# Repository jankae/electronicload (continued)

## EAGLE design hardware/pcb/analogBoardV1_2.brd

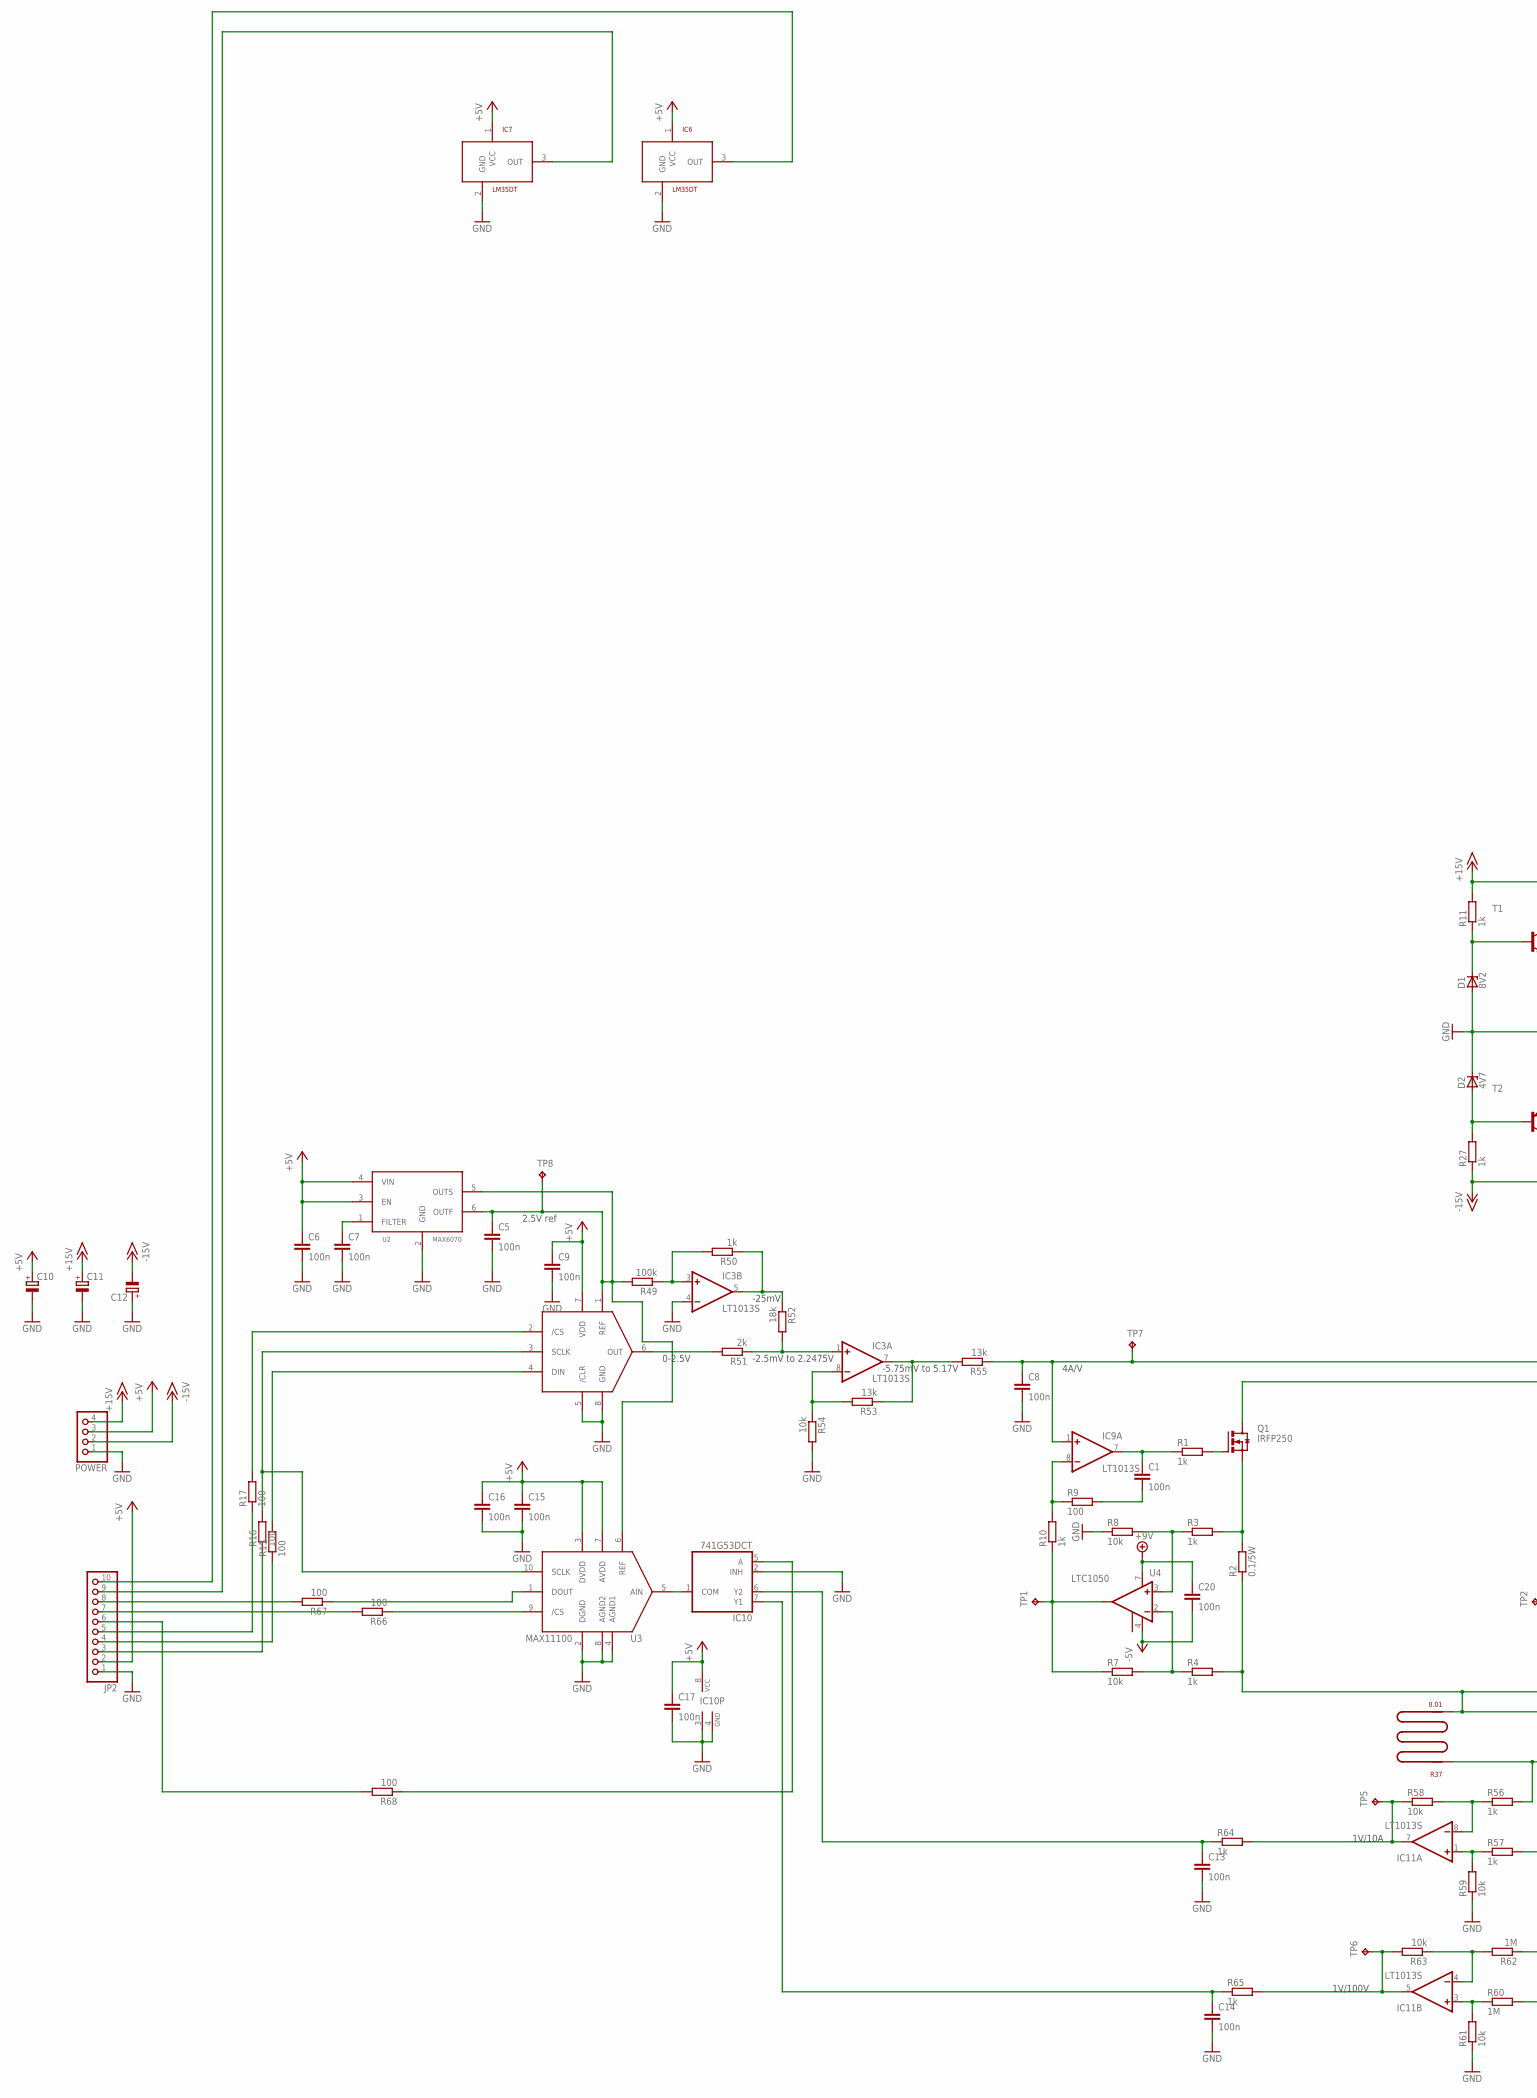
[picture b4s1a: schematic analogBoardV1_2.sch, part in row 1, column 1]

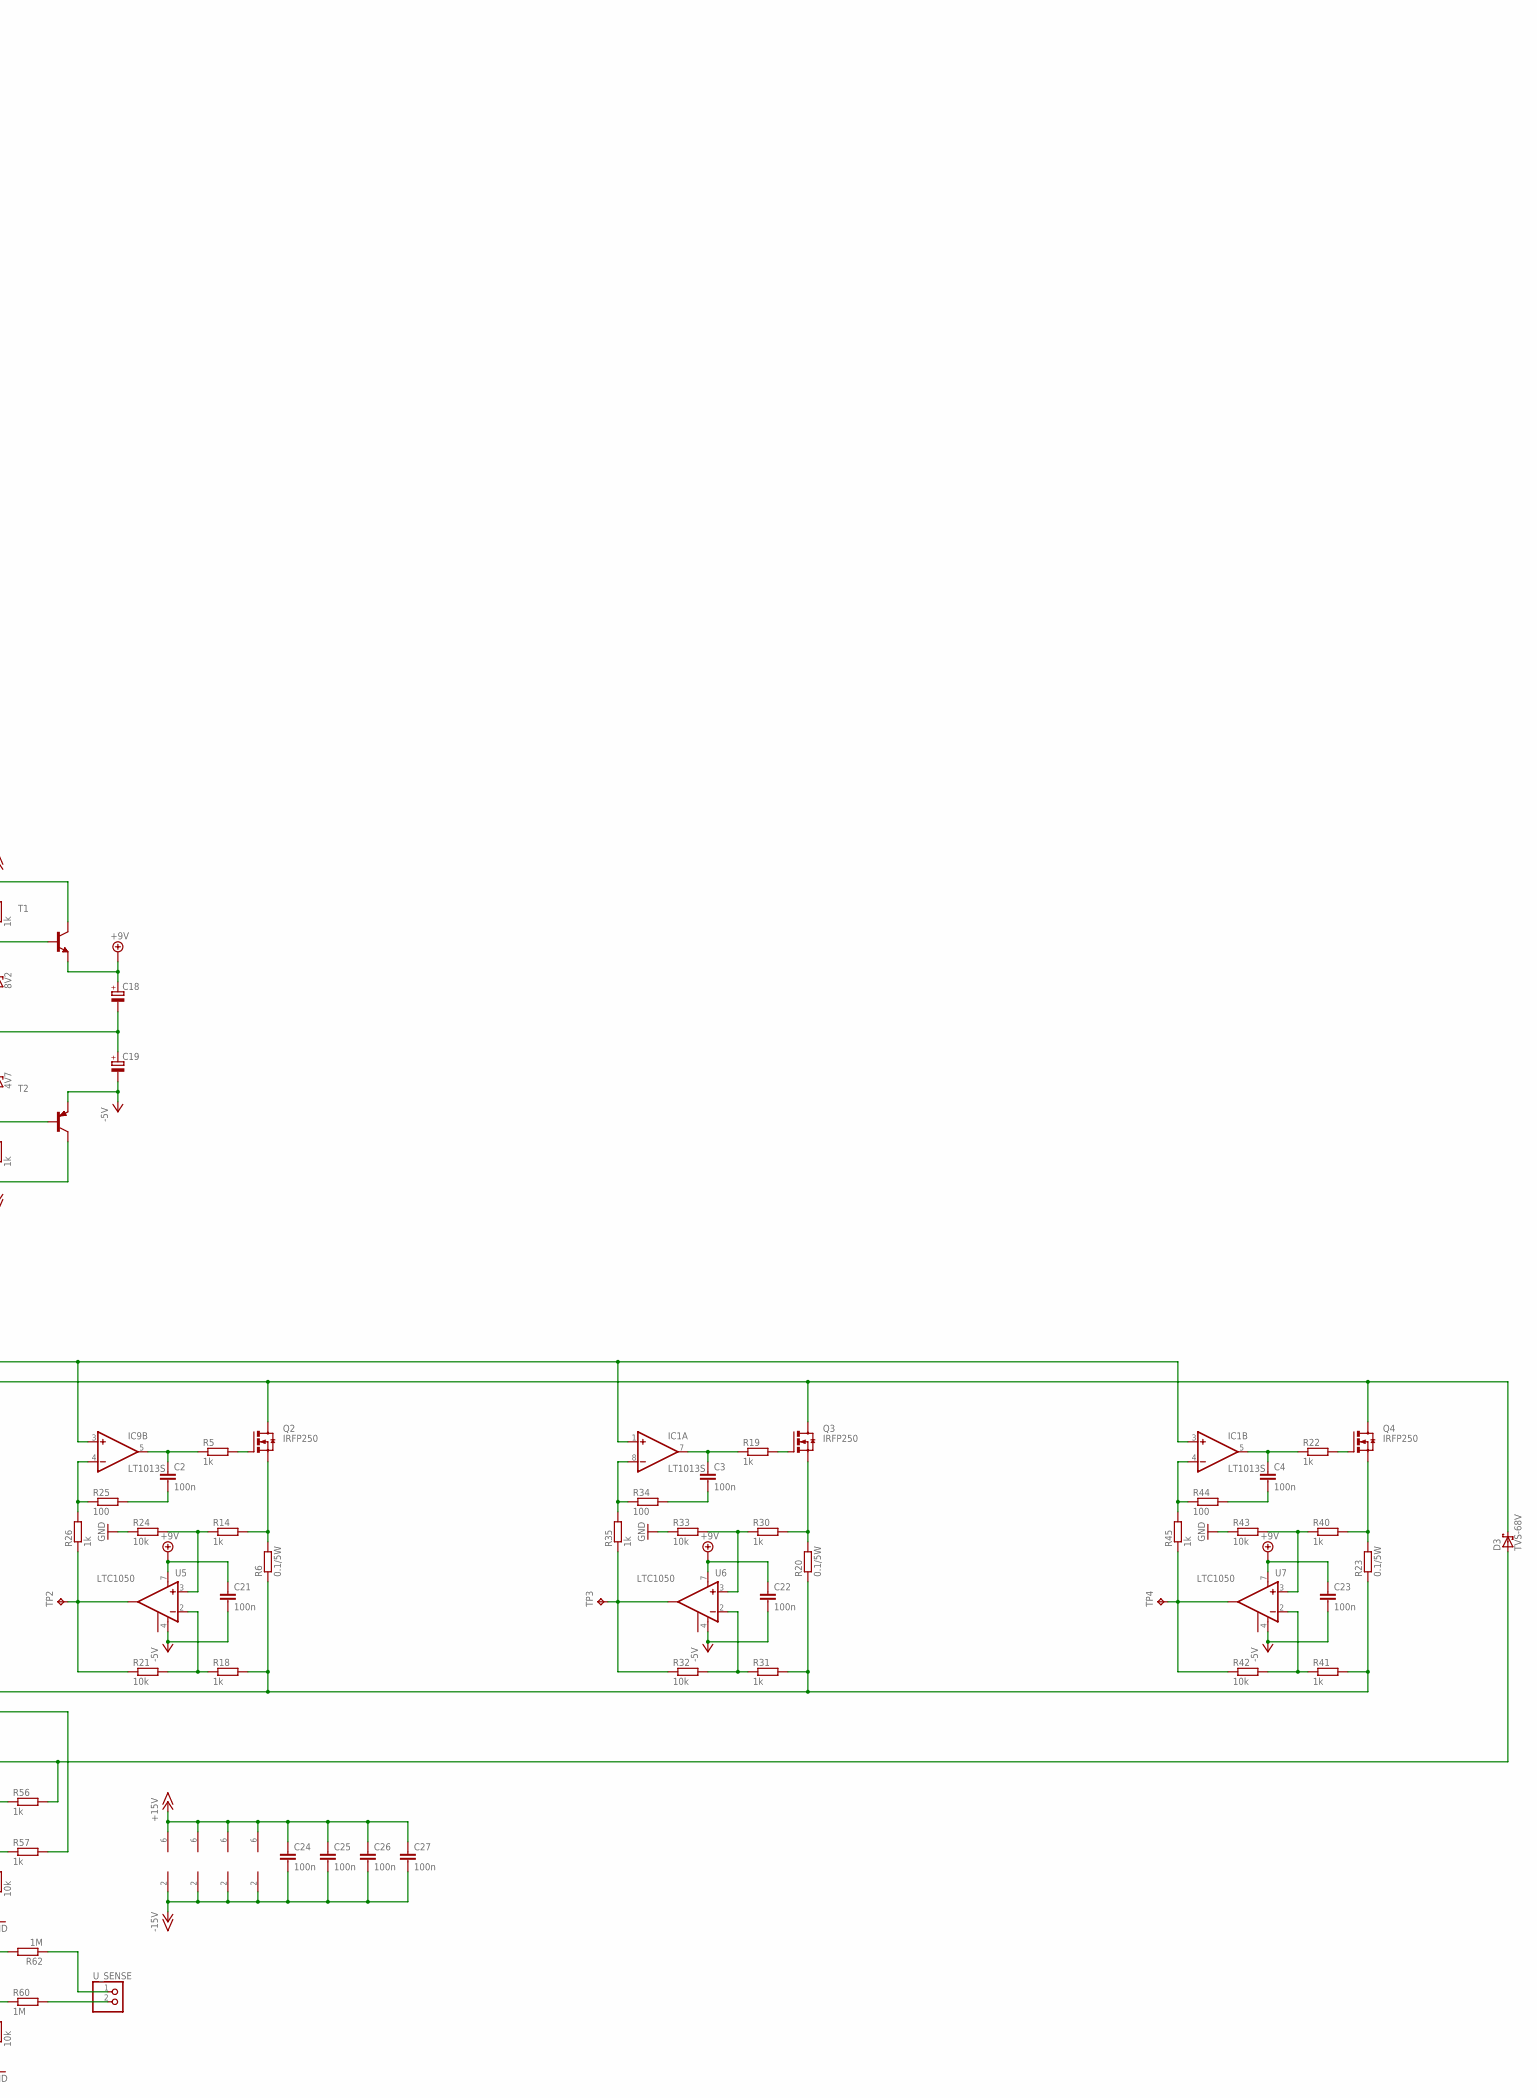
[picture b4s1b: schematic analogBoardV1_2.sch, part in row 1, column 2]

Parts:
C1, C2, C3, C4, C5, C6, C7, C8, C9, C13, C14, C15, C16, C17, C20, C21, C22, C23, C24, C25, C26, C27: 100n; C0603K
C10, C11, C12, C18, C19: CPOL-EUE2.5-6; E2,5-6
D1: 8V2; SOT23
D2: 4V7; SOT23
D3: TVS-68V; CB429-15
IC1, IC3, IC9, IC11: LT1013S; SO08
IC6, IC7: LM35DT; TO220V
IC10: 741G53DCT; DCT_R-PDSO-G8
JP2: PINHD-1X10; 1X10
POWER: PINHD-1X4; 1X04
Q1, Q2, Q3, Q4: IRFP250; TO-247AD-V
R1, R3, R4, R5, R10, R11, R14, R18, R19, R22, R26, R27, R30, R31, R35, R40, R41, R45, R50, R56, R57, R64, R65: 1k; R0603
R2, R6, R20, R23: 0.1/5W; 5WAXIAL
R7, R8, R21, R24, R32, R33, R42, R43, R54, R58, R59, R61, R63: 10k; R0603
R9, R15, R16, R17, R25, R34, R44, R66, R67, R68: 100; R0603
R37: 0.01; COPPERSHUNT
R49: 100k; R0603
R51: 2k; R0603
R52: 18k; R0603
R53, R55: 13k; R0603
R60, R62: 1M; R0603
T1: BC817-16-NPN-SOT23-BEC; SOT23-BEC
T2: BC807-16-PNP-SOT23-BEC; SOT23-BEC
TP1, TP2, TP3, TP4, TP5, TP6, TP7, TP8: TPB1,27; B1,27
U1: MAX5216; UMAX8
U2: MAX6070; SOT23-6L
U3: MAX11100; UMAX10
U4, U5, U6, U7: LTC1050; SOIC8
U_SENSE: PINHD-1X2; 1X02

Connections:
1M: R62.1, U_SENSE.1
+5V: C6.1, C9.1, C10.+, C15.1, C16.1, C17.1, IC6.1 (VCC), IC7.1 (VCC), IC10.8 (VCC), JP2.2, POWER.3, U1.7 (VDD), U2.3 (EN), U2.4 (VIN), U3.3 (DVDD), U3.7 (AVDD)
+9V: C18.+, C20.1, C21.1, C22.1, C23.1, T1.E, U4.7 (V+), U5.7 (V+), U6.7 (V+), U7.7 (V+)
+15V: C11.+, C24.1, C25.1, C26.1, C27.1, IC1.6 (V+), IC3.6 (V+), IC9.6 (V+), IC11.6 (V+), POWER.4, R11.2, T1.C
-5V: C19.-, C20.2, C21.2, C22.2, C23.2, T2.E, U4.4 (V-), U5.4 (V-), U6.4 (V-), U7.4 (V-)
-15V: C12.-, C24.2, C25.2, C26.2, C27.2, IC1.2 (V-), IC3.2 (V-), IC9.2 (V-), IC11.2 (V-), POWER.2, R27.1, T2.C
GND: C5.2, C6.2, C7.2, C8.2, C9.2, C10.-, C11.-, C12.+, C13.2, C14.2, C15.2, C16.2, C17.2, C18.-, C19.+, D1.1 (A), D2.3 (C), IC3.4 (-IN), IC6.2 (GND), IC7.2 (GND), IC10.2 (INH), IC10.3 (GND), IC10.4 (GND), JP2.1, POWER.1, R8.1, R24.1, R33.1, R43.1, R54.2, R59.1, R61.1, U1.5 (/CLR), U1.8 (GND), U2.2 (GND), U3.2 (DGND), U3.4 (AGND1), U3.8 (AGND2)
unnamed: R2.1, R4.2, R6.1, R18.2, R20.1, R23.1, R31.2, R37.P$2, R41.2, R57.2
unnamed: Q1.G, R1.2
unnamed: Q1.S, R2.2, R3.2
unnamed: R4.1, R7.2, U4.2 (-IN)
unnamed: R3.1, R8.2, U4.3 (+IN)
unnamed: Q2.G, R5.2
unnamed: Q2.S, R6.2, R14.2
unnamed: C1.1, IC9.7 (OUT), R1.1
unnamed: C1.2, R9.2
unnamed: R7.1, R10.1, TP1.TP, U4.6 (OUT)
unnamed: IC9.8 (-IN), R9.1, R10.2
unnamed: D1.3 (C), R11.1, T1.B
unnamed: D2.1 (A), R27.2, T2.B
unnamed: Q3.G, R19.2
unnamed: R15.2, U1.4 (DIN)
unnamed: Q3.S, R20.2, R30.2
unnamed: R16.2, U1.3 (SCLK), U3.10 (SCLK)
unnamed: R17.2, U1.2 (/CS)
unnamed: C8.1, IC1.1 (+IN), IC1.3 (+IN), IC9.1 (+IN), IC9.3 (+IN), R55.1, TP7.TP
unnamed: C7.1, U2.1 (FILTER)
unnamed: Q4.G, R22.2
unnamed: Q4.S, R23.2, R40.2
unnamed: C5.1, R49.2, TP8.TP, U1.1 (REF), U2.5 (OUTS), U2.6 (OUTF), U3.6 (REF)
unnamed: R51.2, U1.6 (OUT)
unnamed: R18.1, R21.2, U5.2 (-IN)
unnamed: R14.1, R24.2, U5.3 (+IN)
unnamed: C2.1, IC9.5 (OUT), R5.1
unnamed: C2.2, R25.2
unnamed: R21.1, R26.1, TP2.TP, U5.6 (OUT)
unnamed: IC9.4 (-IN), R25.1, R26.2
unnamed: IC3.3 (+IN), R49.1, R50.2
unnamed: IC3.5 (OUT), R50.1, R52.1
unnamed: IC3.1 (+IN), R51.1, R52.2
unnamed: IC3.8 (-IN), R53.2, R54.1
unnamed: R31.1, R32.2, U6.2 (-IN)
unnamed: R30.1, R33.2, U6.3 (+IN)
unnamed: C3.1, IC1.7 (OUT), R19.1
unnamed: JP2.5, R17.1
unnamed: JP2.3, R16.1
unnamed: JP2.4, R15.1
unnamed: C3.2, R34.2
unnamed: IC6.3 (OUT), JP2.10
unnamed: IC7.3 (OUT), JP2.9
unnamed: R32.1, R35.1, TP3.TP, U6.6 (OUT)
unnamed: IC1.8 (-IN), R34.1, R35.2
unnamed: IC3.7 (OUT), R53.1, R55.2
unnamed: IC10.1 (COM), U3.5 (AIN)
unnamed: R41.1, R42.2, U7.2 (-IN)
unnamed: R40.1, R43.2, U7.3 (+IN)
unnamed: C4.1, IC1.5 (OUT), R22.1
unnamed: C4.2, R44.2
unnamed: R42.1, R45.1, TP4.TP, U7.6 (OUT)
unnamed: IC1.4 (-IN), R44.1, R45.2
unnamed: D3.A, R37.P$1, R56.2
unnamed: IC11.5 (OUT), R63.2, R65.2, TP6.TP
unnamed: IC11.8 (-IN), R56.1, R58.2
unnamed: IC11.1 (+IN), R57.1, R59.2
unnamed: C13.1, IC10.6 (Y2), R64.1
unnamed: IC11.7 (OUT), R58.1, R64.2, TP5.TP
unnamed: R60.2, U_SENSE.2
unnamed: IC11.3 (+IN), R60.1, R61.2
unnamed: IC11.4 (-IN), R62.2, R63.1
unnamed: C14.1, IC10.7 (Y1), R65.1
unnamed: IC10.5 (A), R68.1
unnamed: JP2.7, R66.2
unnamed: R67.1, U3.1 (DOUT)
unnamed: R66.1, U3.9 (/CS)
unnamed: JP2.8, R67.2
unnamed: JP2.6, R68.2
POS_INPUT1: D3.C, Q1.D, Q2.D, Q3.D, Q4.D

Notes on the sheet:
4A/V
0-2.5V
2.5V ref
-25mV
-2.5mV to 2.2475V
-5.75mV to 5.17V
1V/10A
1V/100V

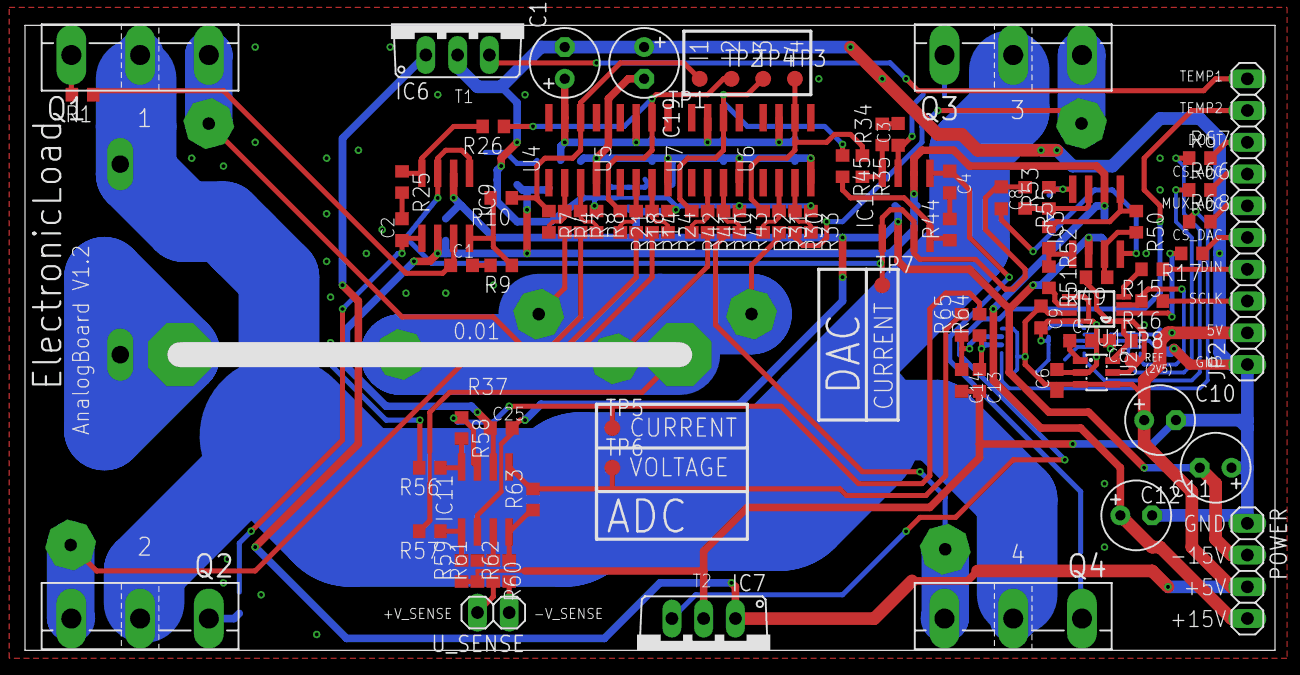
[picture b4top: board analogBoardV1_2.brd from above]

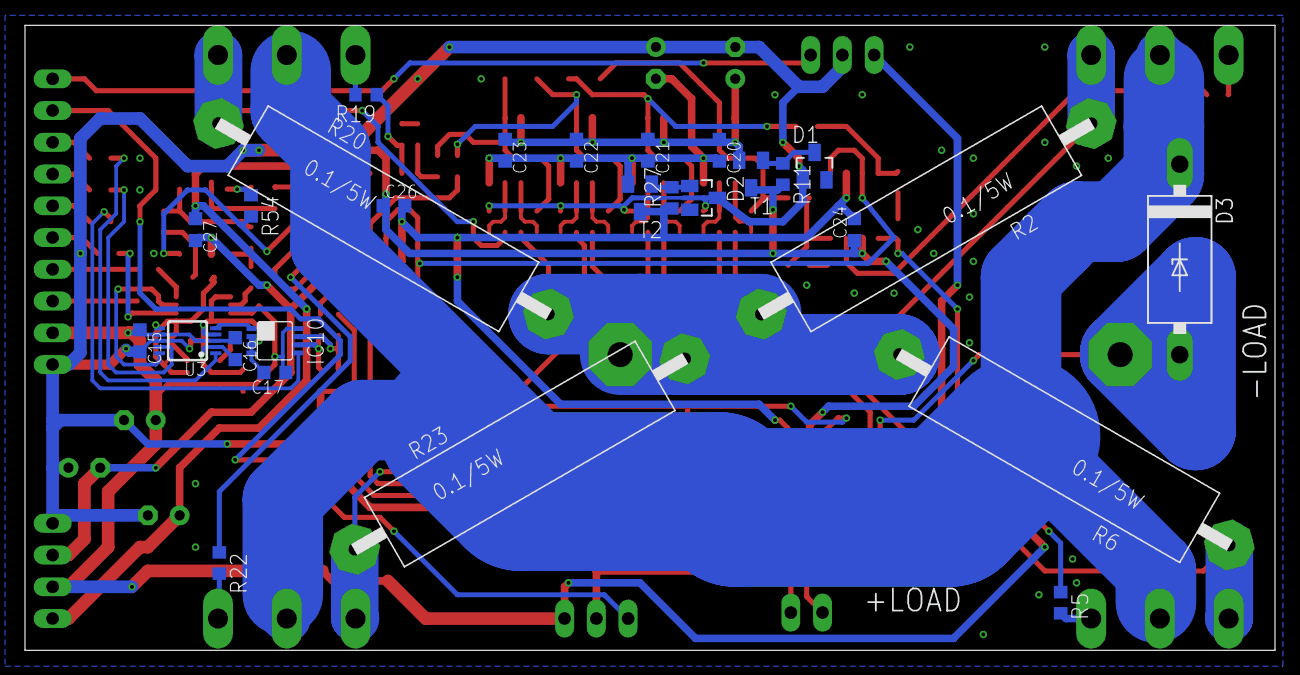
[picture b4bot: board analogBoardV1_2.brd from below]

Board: 2 copper layers, 100.0 x 50.0 mm, 119 parts (27 on the bottom side), 77 nets.

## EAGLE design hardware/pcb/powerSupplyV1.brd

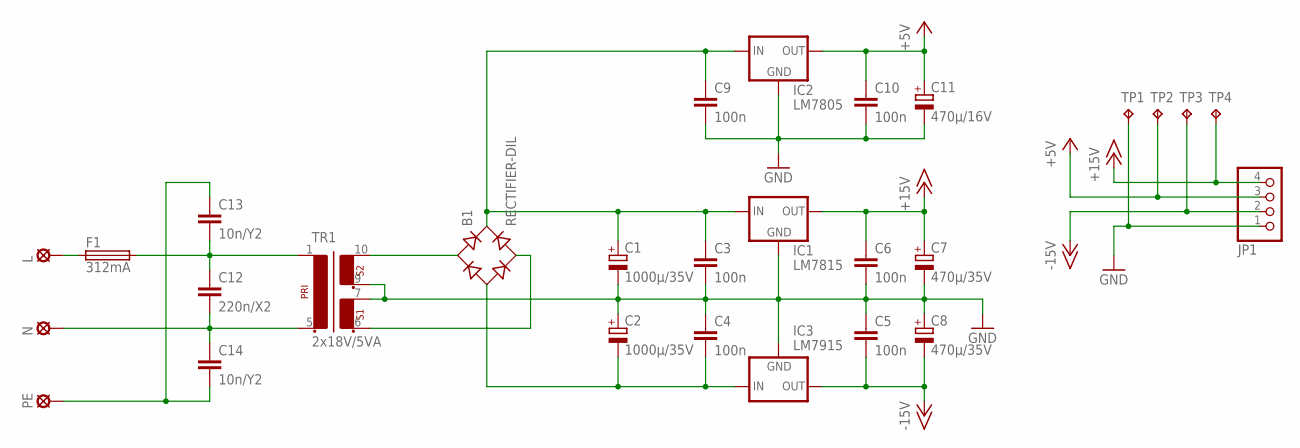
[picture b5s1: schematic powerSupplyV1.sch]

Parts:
B1: RECTIFIER-DIL; B-DIL
C1, C2: 1000µ/35V; E5-13
C3, C4, C5, C6, C9, C10: 100n; C0603K
C7, C8: 470µ/35V; E5-10,5
C11: 470µ/16V; E5-10,5
C12: 220n/X2; C225-062X268
C13, C14: 10n/Y2; C150-054X183
F1: 312mA; SH22,5
IC1: LM7815; 78XXS
IC2: LM7805; 78XXS
IC3: LM7915; 79XXS
JP1: PINHD-1X4; 1X04
L: L; SE14
N: SE14
PE: SE14
TP1, TP2, TP3, TP4: TPB2,54; B2,54
TR1: 2x18V/5VA; EI42-2

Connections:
+5V: C10.1, C11.+, IC2.OUT, JP1.3, TP2.TP
+15V: C6.1, C7.+, IC1.OUT, JP1.4, TP4.TP
-15V: C5.2, C8.-, IC3.OUT, JP1.2, TP3.TP
GND: C1.-, C2.+, C3.2, C4.1, C5.1, C6.2, C7.-, C8.+, C9.2, C10.2, C11.-, IC1.GND, IC2.GND, IC3.GND, JP1.1, TP1.TP, TR1.7 (4), TR1.9 (5)
unnamed: B1.AC1, TR1.10 (6)
unnamed: B1.AC2, TR1.6 (3)
unnamed: C12.1, C13.2, F1.2, TR1.1
unnamed: B1.-, C2.-, C4.2, IC3.IN
unnamed: B1.+, C1.+, C3.1, C9.1, IC1.IN, IC2.IN
unnamed: C12.2, C14.1, N.MP, TR1.5 (2)
unnamed: C13.1, C14.2, PE.MP
unnamed: F1.1, L.MP

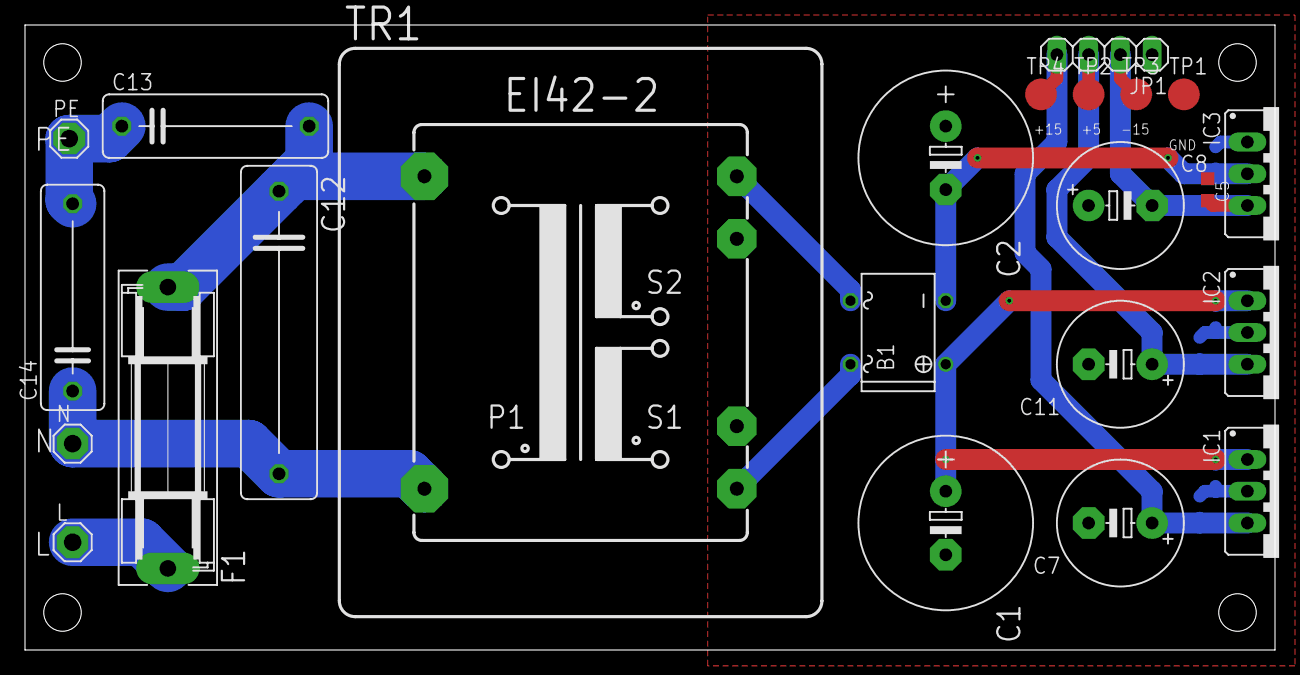
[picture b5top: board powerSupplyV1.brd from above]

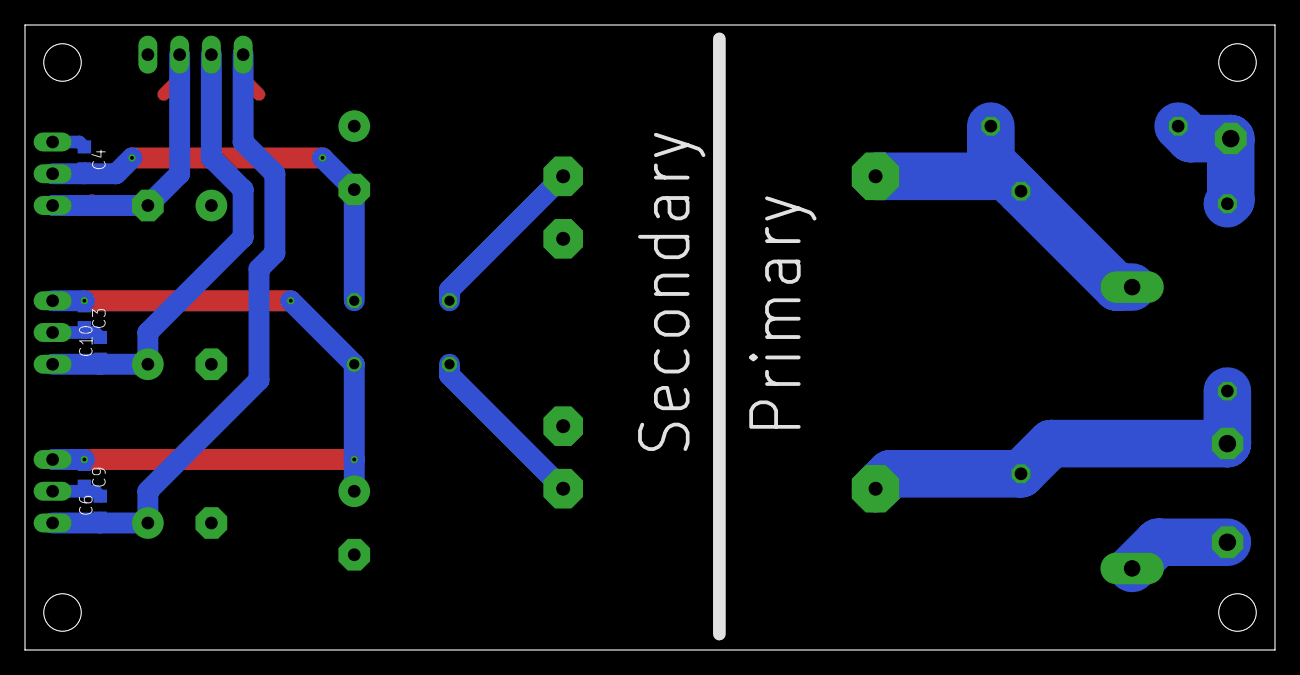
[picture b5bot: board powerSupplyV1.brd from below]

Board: 2 copper layers, 100.0 x 50.0 mm, 28 parts (5 on the bottom side), 12 nets.

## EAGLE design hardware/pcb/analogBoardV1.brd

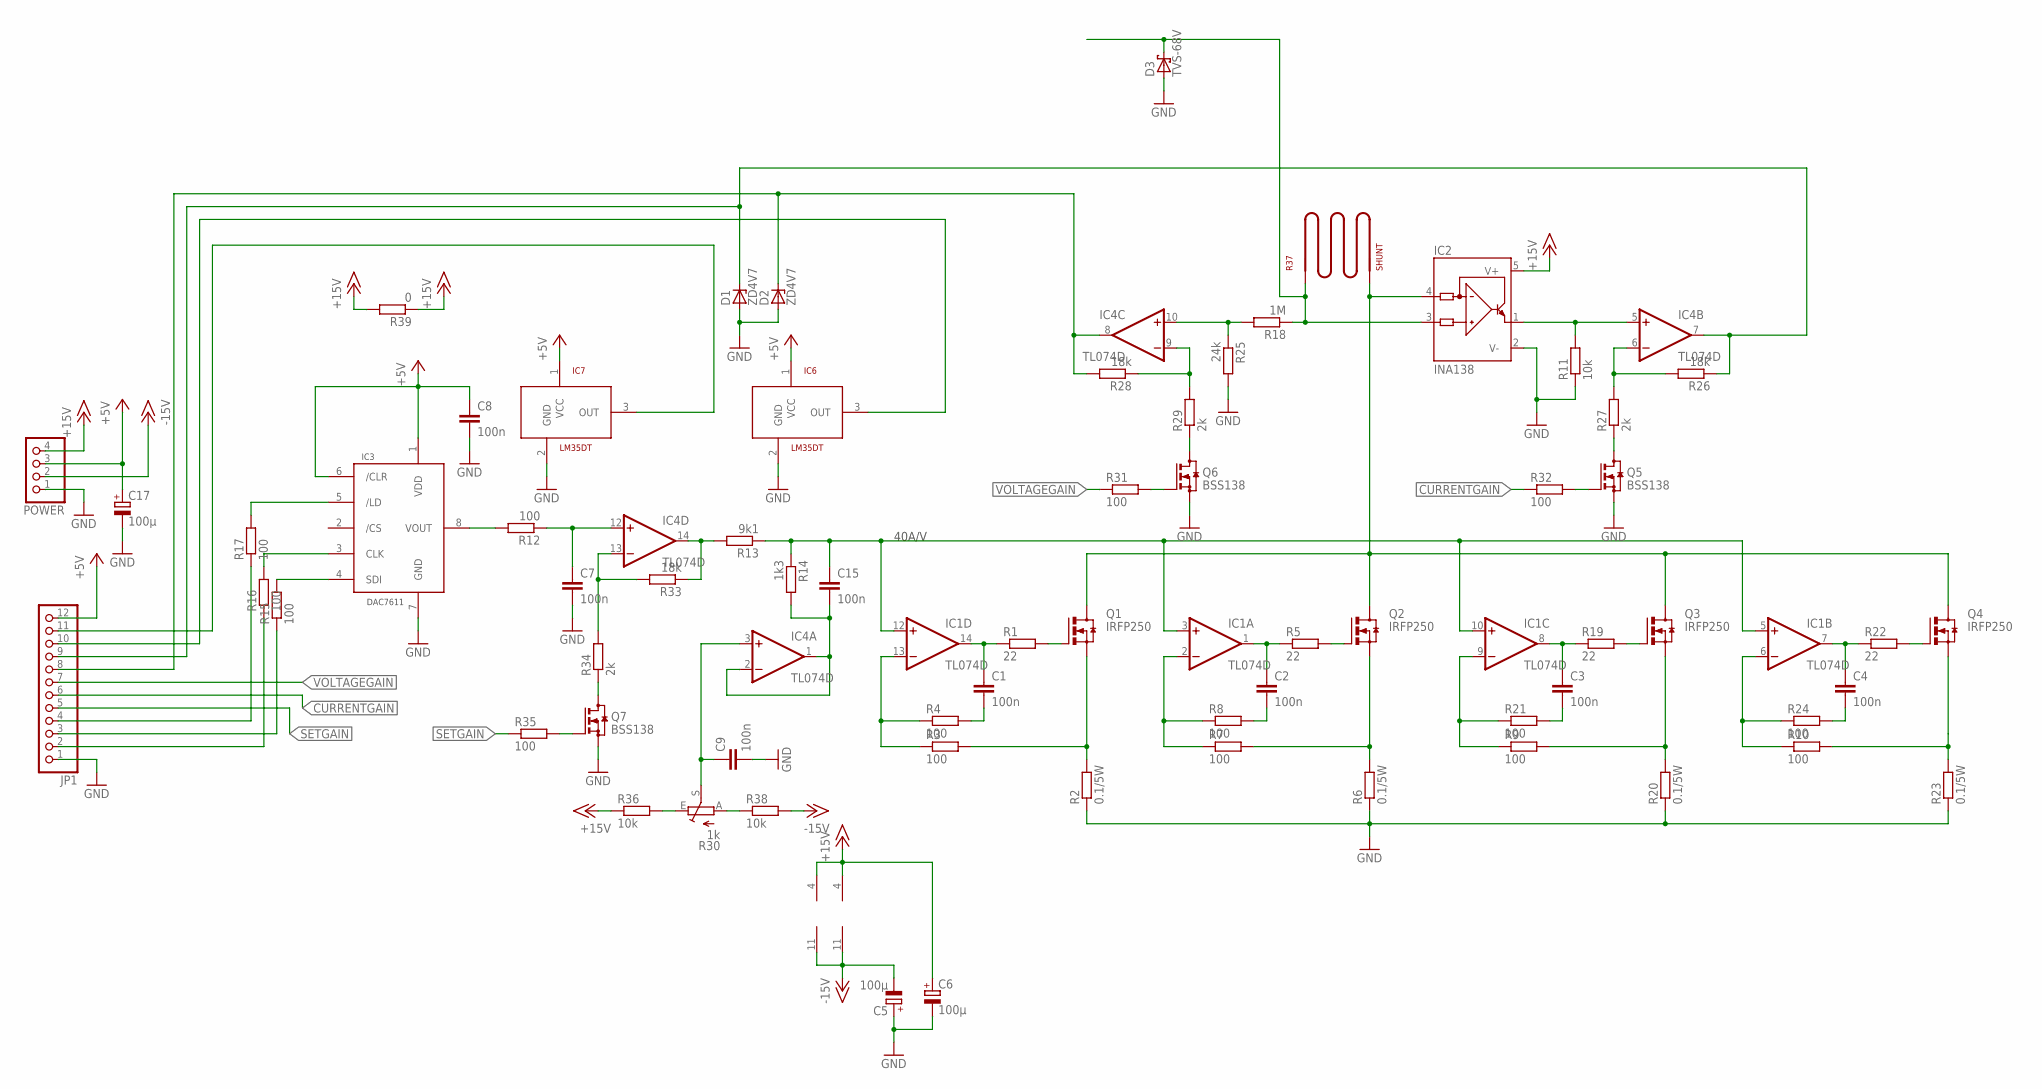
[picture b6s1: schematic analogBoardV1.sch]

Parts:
C1, C2, C3, C4, C7, C8, C9, C15: 100n; C0603K
C5, C6, C17: 100µ; E2,5-6
D1, D2: ZD4V7; SOT23
D3: TVS-68V; CB429-15
IC1, IC4: TL074D; SO14
IC2: INA138; SOT23-5
IC3: DAC7611; SO8
IC6, IC7: LM35DT; TO220V
JP1: PINHD-1X12; 1X12
POWER: PINHD-1X4; 1X04
Q1, Q2, Q3, Q4: IRFP250; TO-247AD-V
Q5, Q6, Q7: BSS138; SOT23
R1, R5, R19, R22: 22; R0603
R2, R6, R20, R23: 0.1/5W; 5WAXIAL
R3, R4, R7, R8, R9, R10, R12, R15, R16, R17, R21, R24, R31, R32, R35: 100; R0603
R11, R36, R38: 10k; R0603
R13: 9k1; R0603
R14: 1k3; R0603
R18: 1M; R0603
R25: 24k; R0603
R26, R28, R33: 18k; R0603
R27, R29, R34: 2k; R0603
R30: 1k; RJ9W
R37: SHUNT; COPPERSHUNT
R39: 0; R1206

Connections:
10: IC4.9 (-IN), R28.1, R29.2
+5V: C8.1, C17.+, IC3.1 (VDD), IC3.6 (/CLR), IC6.1 (VCC), IC7.1 (VCC), JP1.12, POWER.3
+15V: C6.+, IC1.4 (V+), IC2.5 (V+), IC4.4 (V+), POWER.4, R36.1, R39.1, R39.2
-15V: C5.-, IC1.11 (V-), IC4.11 (V-), POWER.2, R38.2
CURRENTGAIN: JP1.6, R32.1
GND: C5.+, C6.-, C7.2, C8.2, C9.2, C17.-, D1.1 (A), D2.1 (A), D3.A, IC2.2 (V-), IC3.7 (GND), IC6.2 (GND), IC7.2 (GND), JP1.1, POWER.1, Q5.2 (S), Q6.2 (S), Q7.2 (S), R2.1, R6.1, R11.1, R20.1, R23.1, R25.2
unnamed: C1.1, IC1.14 (OUT), R1.1
unnamed: Q1.G, R1.2
unnamed: Q1.S, R2.2, R3.2
unnamed: C1.2, R4.2
unnamed: IC1.13 (-IN), R3.1, R4.1
unnamed: C2.1, IC1.1 (OUT), R5.1
unnamed: Q2.G, R5.2
unnamed: Q2.S, R6.2, R7.2
unnamed: IC1.2 (-IN), R7.1, R8.1
unnamed: C2.2, R8.2
unnamed: D3.C, IC2.3 (IN+), R18.1, R37.P$1
unnamed: IC2.1 (OUT), IC4.5 (+IN), R11.2
unnamed: IC3.8 (VOUT), R12.2
unnamed: C3.1, IC1.8 (OUT), R19.1
unnamed: Q3.G, R19.2
unnamed: C7.1, IC4.12 (+IN), R12.1
unnamed: IC4.14 (OUT), R13.2, R33.1
unnamed: IC3.4 (SDI), R15.2
unnamed: Q3.S, R9.2, R20.2
unnamed: IC1.9 (-IN), R9.1, R21.1
unnamed: IC3.3 (CLK), R16.2
unnamed: IC3.5 (/LD), R17.2
unnamed: C3.2, R21.2
unnamed: C4.1, IC1.7 (OUT), R22.1
unnamed: D1.3 (C), IC4.7 (OUT), JP1.9, R26.1
unnamed: Q4.G, R22.2
unnamed: Q4.S, R10.2, R23.2
unnamed: IC1.6 (-IN), R10.1, R24.1
unnamed: C4.2, R24.2
unnamed: C15.2, IC4.1 (OUT), IC4.2 (-IN), R14.2
unnamed: C15.1, IC1.3 (+IN), IC1.5 (+IN), IC1.10 (+IN), IC1.12 (+IN), R13.1, R14.1
unnamed: R30.A, R38.1
unnamed: IC4.10 (+IN), R18.2, R25.1
unnamed: R30.E, R36.2
unnamed: IC4.6 (-IN), R26.2, R27.2
unnamed: Q5.3 (D), R27.1
unnamed: Q6.3 (D), R29.1
unnamed: D2.3 (C), IC4.8 (OUT), JP1.8, R28.2
unnamed: Q5.1 (G), R32.2
unnamed: Q6.1 (G), R31.2
unnamed: IC4.13 (-IN), R33.2, R34.2
unnamed: Q7.3 (D), R34.1
unnamed: Q7.1 (G), R35.2
unnamed: C9.1, IC4.3 (+IN), R30.S
unnamed: JP1.4, R17.1
unnamed: JP1.2, R16.1
unnamed: JP1.3, R15.1
unnamed: IC6.3 (OUT), JP1.10
unnamed: IC7.3 (OUT), JP1.11
POS_INPUT1: IC2.4 (IN-), Q1.D, Q2.D, Q3.D, Q4.D, R37.P$2
SETGAIN: JP1.5, R35.1
VOLTAGEGAIN: JP1.7, R31.1

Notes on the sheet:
40A/V

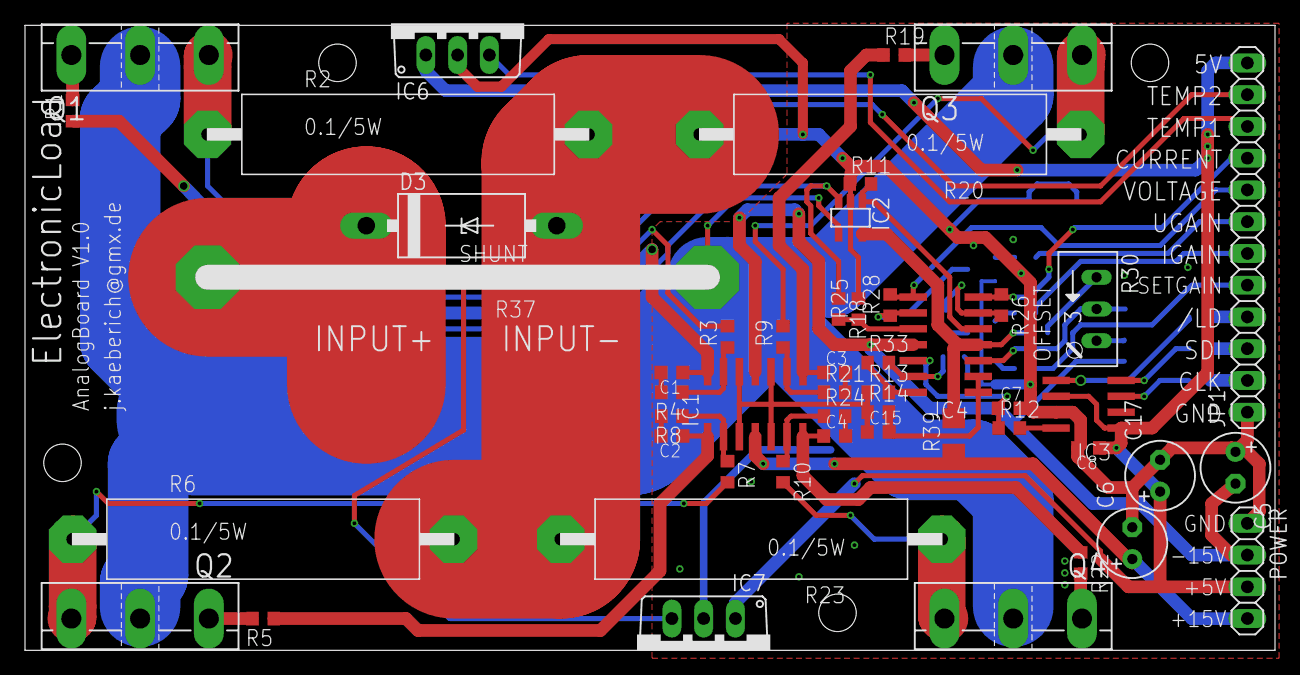
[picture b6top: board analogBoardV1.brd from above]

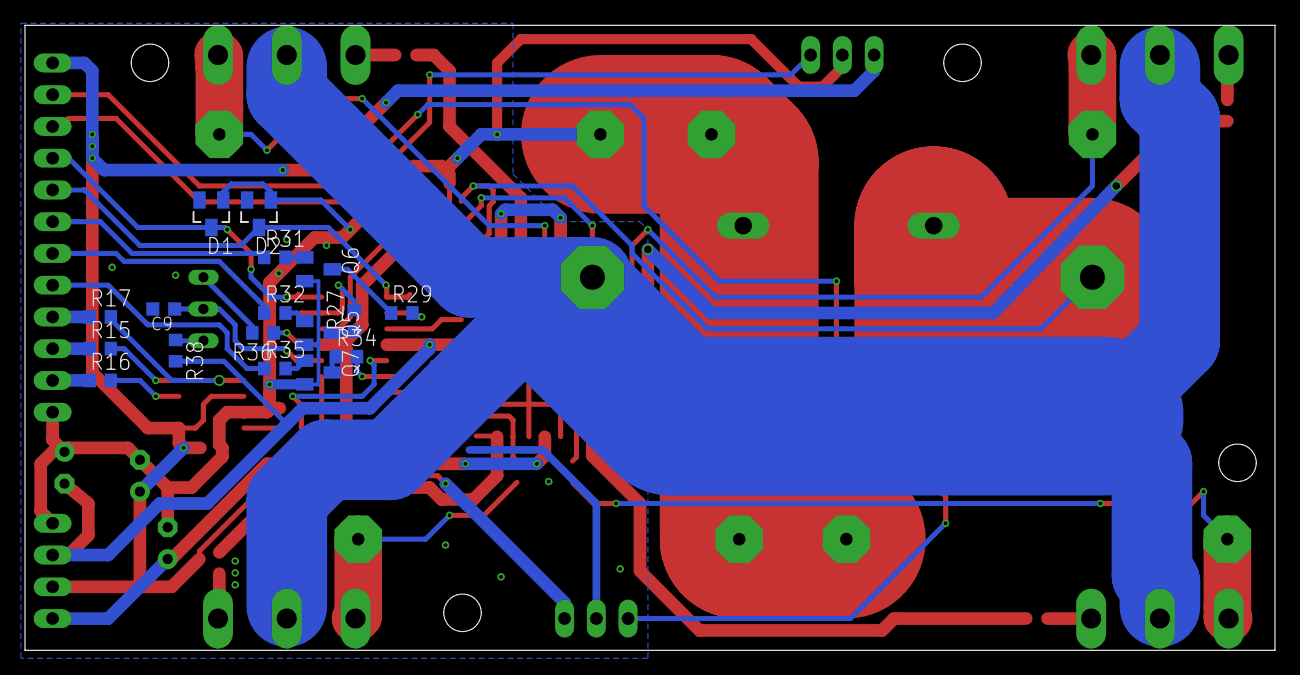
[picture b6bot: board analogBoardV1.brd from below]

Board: 2 copper layers, 100.0 x 50.0 mm, 68 parts (17 on the bottom side), 58 nets.
